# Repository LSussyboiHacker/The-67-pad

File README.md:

The 67 pad

My custom macropad. Took me a while to learn the basics of everything, but making the github repo was the most frustrating, atleast I've got it working now. I plan to use it for general editing and as a soundboard.

BOM

- 15x Blank DSA Keycaps
- 4x M3x16 Bolt
- 4x M3 Heatset
- 1x XIAO RP2040
- 15x Cherry MX Switches
- 1x 3D printed case (top and bottom)
- 1x 0.91 inch OLED display
  
Case

PCB

Schematic

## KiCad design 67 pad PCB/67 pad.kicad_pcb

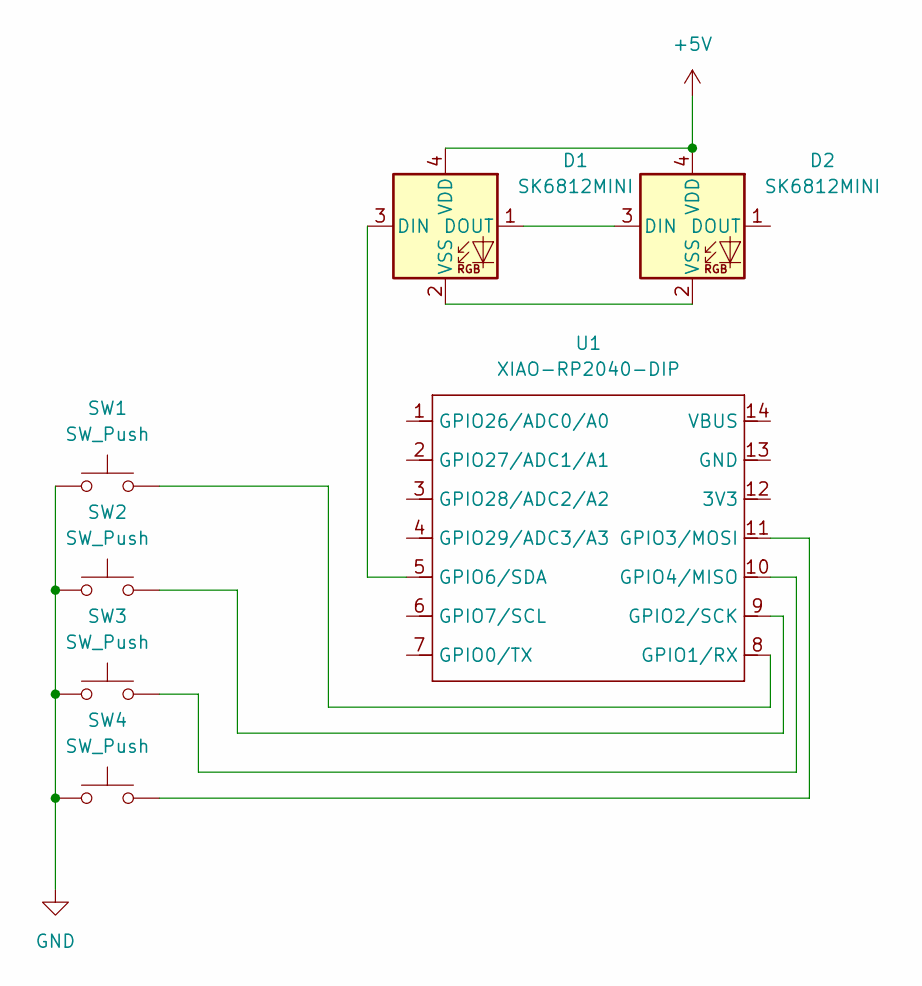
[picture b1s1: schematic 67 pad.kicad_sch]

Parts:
D1, D2: SK6812MINI; LED_SK6812MINI_PLCC4_3.5x3.5mm_P1.75mm
SW1, SW2, SW3, SW4: SW_Push; SW_Cherry_MX_1.00u_PCB
U1: XIAO-RP2040-DIP

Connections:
+5V: D1.4 (VDD), D2.4 (VDD)
GND: SW1.1, SW2.1, SW3.1, SW4.1
unnamed: D1.3 (DIN), U1.5 (GPIO6/SDA)
unnamed: D1.1 (DOUT), D2.3 (DIN)
unnamed: D1.2 (VSS), D2.2 (VSS)
unnamed: SW1.2, U1.8 (GPIO1/RX)
unnamed: SW2.2, U1.9 (GPIO2/SCK)
unnamed: SW4.2, U1.11 (GPIO3/MOSI)
unnamed: SW3.2, U1.10 (GPIO4/MISO)

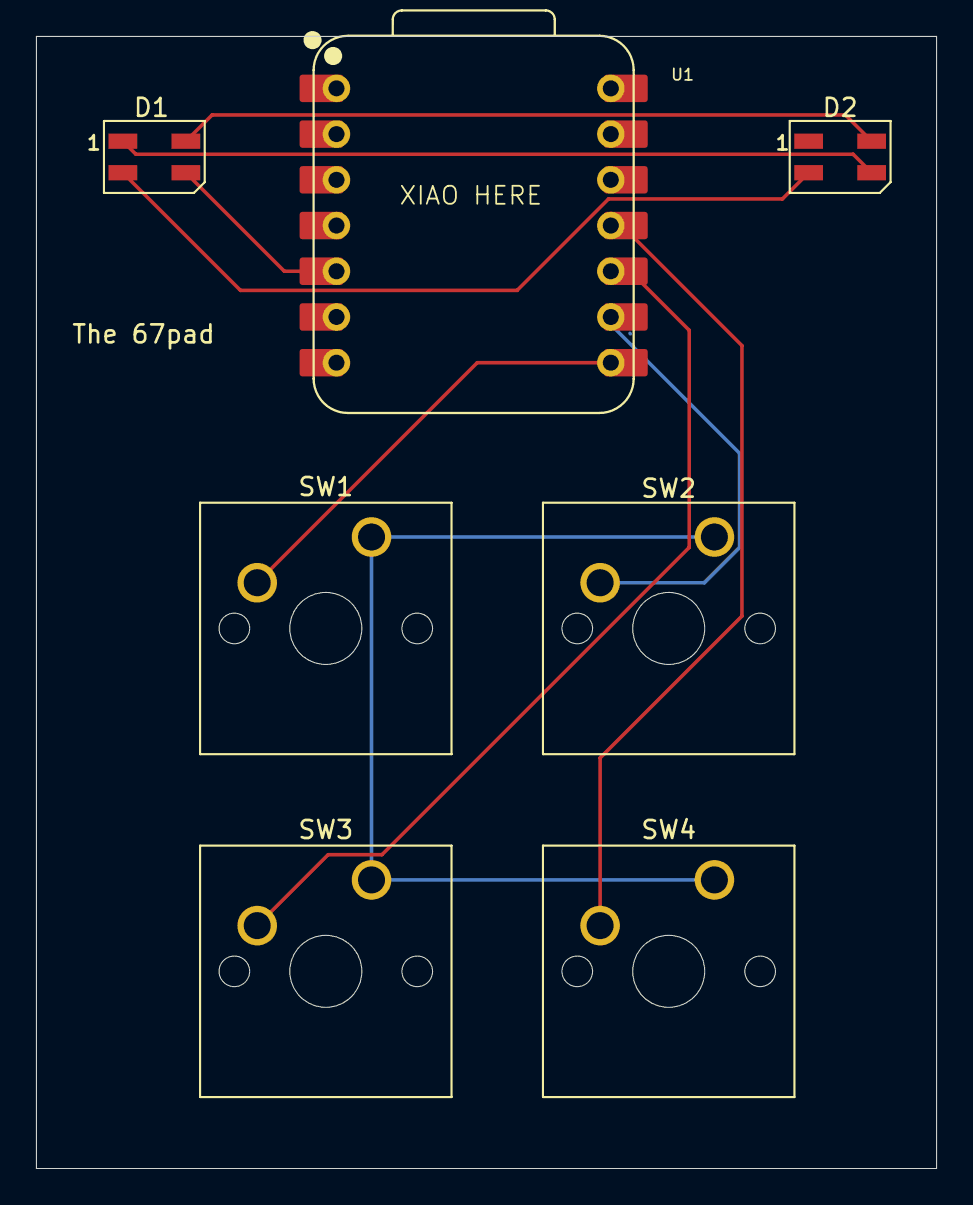
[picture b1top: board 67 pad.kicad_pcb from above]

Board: 2 copper layers, 50.0 x 62.9 mm, 7 parts (0 on the bottom side), 9 nets.

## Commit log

2025-12-24 Add project overview and bill of materials
    Added initial project description and BOM list.
2025-12-24 Update README with project introduction and BOM
    Added a brief introduction and BOM list to the README.
2025-12-24 Revise README with macropad details and images
    Updated the description of the macropad and added images for case, PCB, and schematic.
2025-12-24 Fix formatting of the project title in README
